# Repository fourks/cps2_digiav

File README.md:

CPS2 digital AV interface (Rev 2 - CPS1 branch)
==============

Features (current)
--------------------------
* framelocked 1080p@59.64Hz output with max. 40 scanline latency
* 24bit/48kHz audio output

TODO
--------------------------
* OSD/UI
* resolution select
* more scanline options
* settings store / profiles

Installation
--------------------------
The add-on board can be installed on top of CPS1 A-board. The following additional parts are required:

* cps1_adapter PCB and related parts, see pcb_cps1_adapter folder
* 3pcs 2x5 U-type pin headers
* ribbon cable
* coaxial cable (~40cm)

Installation instructions are found in pcb/doc/install.md .

Usage
--------------------------
Board is controlled via two external buttons:
* BTN1: change vertical offset (0-8, default=4)
* BTN2: enable/disable scanlines

More info and discussion
--------------------------
* [Forum topic](http://shmups.system11.org/viewtopic.php?f=6&t=59479&p=1266977)

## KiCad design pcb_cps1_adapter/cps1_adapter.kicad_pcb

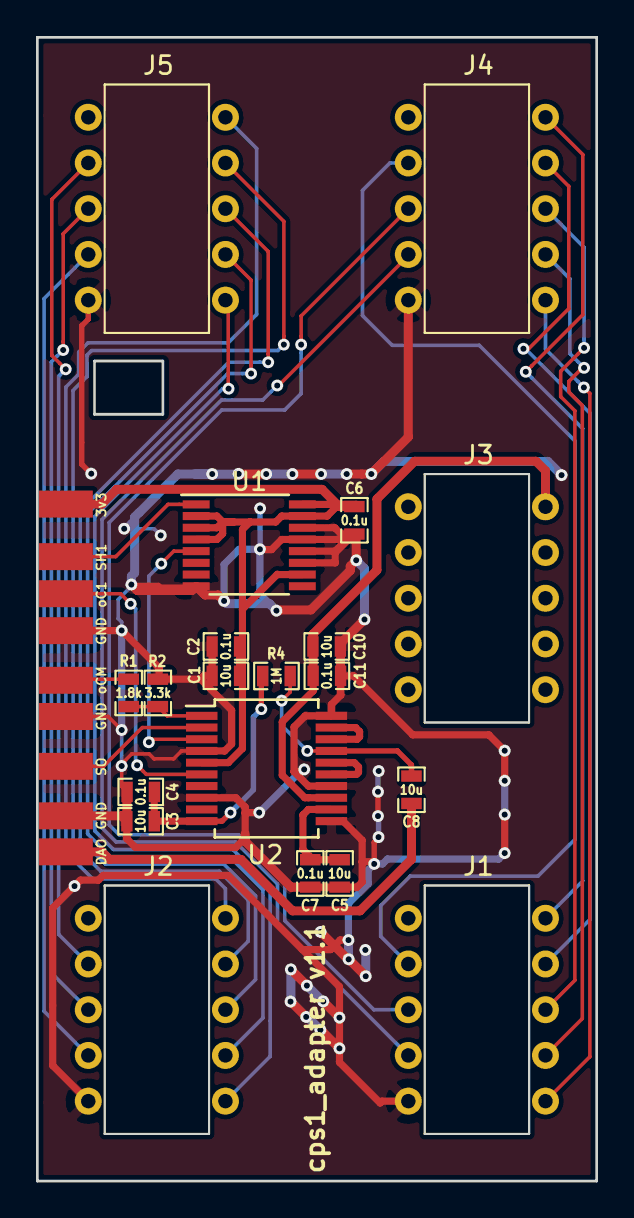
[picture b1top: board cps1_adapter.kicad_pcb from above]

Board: 2 copper layers, 31.1 x 63.5 mm, 29 parts (0 on the bottom side), 31 nets.

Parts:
C1, C3, C5, C8, C10: 10u; SM0603_Capa_libcms
C2, C4, C6, C7, C11: 0.1u; SM0603_Capa_libcms
J1, J2, J3, J4, J5: Conn_02x05_Counter_Clockwise; HLE-105-02-G-DV-PE
R1: 1.8k; SM0603_Resistor_libcms
R2: 3.3k; SM0603_Resistor_libcms
R4: 1M; SM0603_Resistor_libcms
TP1, TP5, TP8: GND; SMD_PAD
TP2: DAO; SMD_PAD
TP3: 3v3; SMD_PAD
TP4: SO; SMD_PAD
TP6: oC1; SMD_PAD
TP7: SH1; SMD_PAD
TP9: oCM; SMD_PAD
U1: 74LVC112; TSSOP-16_4.4x5mm_P0.65mm
U2: WM8782; SSOP-20_5.3x7.2mm_P0.65mm

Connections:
/B0: J1.2, J4.2
/B1: J1.3, J4.3
/B2: J1.4, J4.4
/B3: J1.6, J4.6
/DAO: C8.1, TP2.1
/DVDD3V3: C1.1, C2.1, C6.1, TP3.1, U1.2, U1.3, U1.4, U1.10, U1.15, U1.16, U2.5
/DVDD5V: C10.1, C11.1, J3.10, U2.13
/F0: J2.7, J5.7
/F1: J2.8, J5.8
/F2: J2.9, J5.9
/F3: J2.10, J5.10
/G0: J1.7, J4.7
/G1: J1.8, J4.8
/G2: J1.9, J4.9
/G3: J1.10, J4.10
/LRCLK: U1.5, U2.3
/R0: J2.2, J5.2
/R1: J2.3, J5.3
/R2: J2.4, J5.4
/R3: J2.6, J5.6
/SH1: TP7.1, U1.1
/SO: TP4.1, U2.2
/VMID: C3.1, C4.1, R4.1, U2.10
/oC1: TP6.1, U2.6
/oCM: R1.1, TP9.1
GND: C1.2, C2.2, C3.2, C4.2, C5.2, C6.2, C7.2, C10.2, C11.2, J1.5, J2.5, J4.5, J5.5, R2.2, TP1.1, TP5.1, TP8.1, U1.8, U1.11, U1.12, U1.13, U1.14, U2.4, U2.8, U2.11, U2.14, U2.20
unnamed: C5.1, C7.1, U2.12
unnamed: C8.2, R4.2, U2.17
unnamed: R1.2, R2.1, U2.1
unnamed: U2.15, U2.16
unnamed: U2.18, U2.19

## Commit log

2018-09-11 initial adaptation for cps3
2018-10-16 add support for cps3 widescreen mode
2018-10-16 remove files not needed for cps3 adaptation
2018-12-28 clean up and fine-tune cps3 implementation
2018-12-28 remove pcb files from cps3 branch
2018-12-30 update jic and add installation instructions
2019-03-10 port audio ASRC implementation from main branch
2019-06-08 add cps1 branch
2019-07-23 fix random startup problem
2019-07-23 fix audio channel ordering
2019-07-29 restore pushbutton functionality
2019-08-01 update install instructions
2019-08-27 update BOM and instructions
2019-09-26 remove pcb files from cps1 branch
